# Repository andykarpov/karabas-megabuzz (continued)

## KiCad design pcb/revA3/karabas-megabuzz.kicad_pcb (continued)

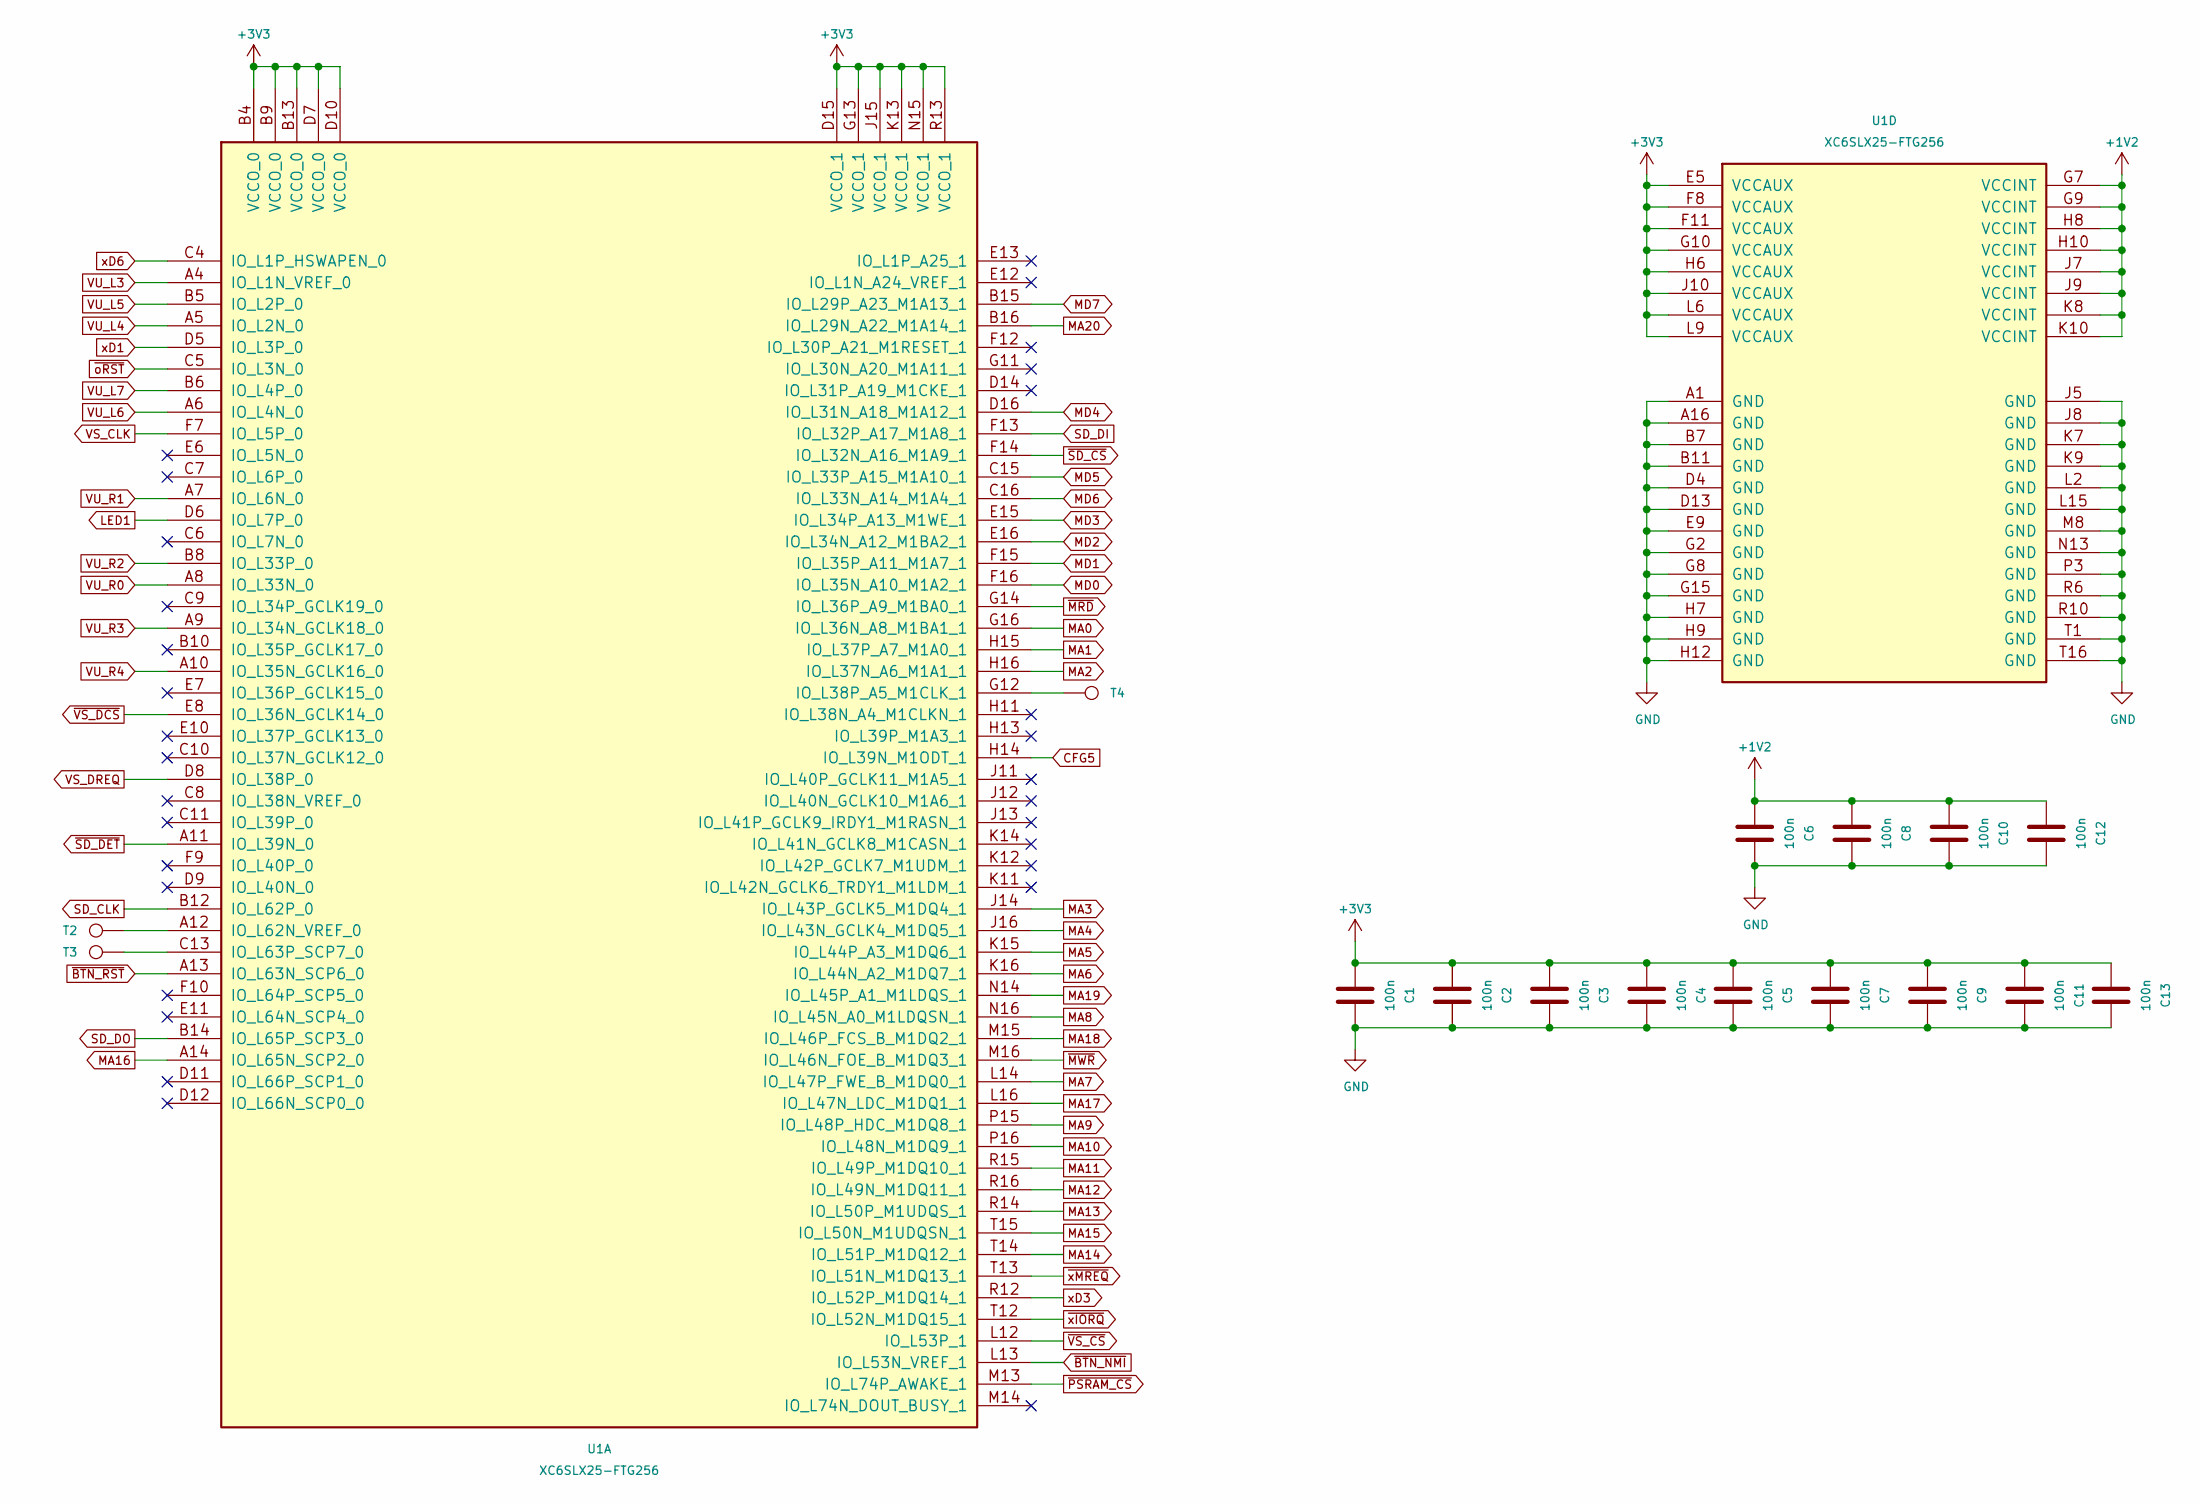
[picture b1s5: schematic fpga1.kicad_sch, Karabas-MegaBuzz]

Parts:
C1, C2, C3, C4, C5, C7, C9, C11, C13: 100n; C_0603_1608Metric_Pad1.08x0.95mm_HandSolder
C6, C8, C10, C12: 100n; C_0603_1608Metric
T2: TestPoint2; TestPoint_Pad_D1.5mm
T3, T4: TestPoint; TestPoint_Pad_D1.5mm
U1: XC6SLX25-FTG256; BGA-256_17.0x17.0mm_Layout16x16_P1.0mm_Ball0.5mm_Pad0.4mm_N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

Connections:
+1V2: C6.1, C8.1, C10.1, C12.1, U1.G7 (VCCINT), U1.G9 (VCCINT), U1.H8 (VCCINT), U1.H10 (VCCINT), U1.J7 (VCCINT), U1.J9 (VCCINT), U1.K8 (VCCINT), U1.K10 (VCCINT); also elsewhere on the board
+3V3: C1.1, C2.1, C3.1, C4.1, C5.1, C7.1, C9.1, C11.1, C13.1, U1.B4 (VCCO_0), U1.B9 (VCCO_0), U1.B13 (VCCO_0), U1.D7 (VCCO_0), U1.D10 (VCCO_0), U1.D15 (VCCO_1), U1.E5 (VCCAUX), U1.F8 (VCCAUX), U1.F11 (VCCAUX), U1.G10 (VCCAUX), U1.G13 (VCCO_1), U1.H6 (VCCAUX), U1.J10 (VCCAUX), U1.J15 (VCCO_1), U1.K13 (VCCO_1), U1.L6 (VCCAUX), U1.L9 (VCCAUX), U1.N15 (VCCO_1), U1.R13 (VCCO_1); also elsewhere on the board
CFG5: U1.H14 (IO_L39N_M1ODT_1); also elsewhere on the board
GND: C1.2, C2.2, C3.2, C4.2, C5.2, C6.2, C7.2, C8.2, C9.2, C10.2, C11.2, C12.2, C13.2, U1.A1 (GND), U1.A16 (GND), U1.B7 (GND), U1.B11 (GND), U1.D4 (GND), U1.D13 (GND), U1.E9 (GND), U1.G2 (GND), U1.G8 (GND), U1.G15 (GND), U1.H7 (GND), U1.H9 (GND), U1.H12 (GND), U1.J5 (GND), U1.J8 (GND), U1.K7 (GND), U1.K9 (GND), U1.L2 (GND), U1.L15 (GND), U1.M8 (GND), U1.N13 (GND), U1.P3 (GND), U1.R6 (GND), U1.R10 (GND), U1.T1 (GND), U1.T16 (GND); also elsewhere on the board
LED1: U1.D6 (IO_L7P_0); also elsewhere on the board
MA0: U1.G16 (IO_L36N_A8_M1BA1_1); also elsewhere on the board
MA1: U1.H15 (IO_L37P_A7_M1A0_1); also elsewhere on the board
MA2: U1.H16 (IO_L37N_A6_M1A1_1); also elsewhere on the board
MA3: U1.J14 (IO_L43P_GCLK5_M1DQ4_1); also elsewhere on the board
MA4: U1.J16 (IO_L43N_GCLK4_M1DQ5_1); also elsewhere on the board
MA5: U1.K15 (IO_L44P_A3_M1DQ6_1); also elsewhere on the board
MA6: U1.K16 (IO_L44N_A2_M1DQ7_1); also elsewhere on the board
MA7: U1.L14 (IO_L47P_FWE_B_M1DQ0_1); also elsewhere on the board
MA8: U1.N16 (IO_L45N_A0_M1LDQSN_1); also elsewhere on the board
MA9: U1.P15 (IO_L48P_HDC_M1DQ8_1); also elsewhere on the board
MA10: U1.P16 (IO_L48N_M1DQ9_1); also elsewhere on the board
MA11: U1.R15 (IO_L49P_M1DQ10_1); also elsewhere on the board
MA12: U1.R16 (IO_L49N_M1DQ11_1); also elsewhere on the board
MA13: U1.R14 (IO_L50P_M1UDQS_1); also elsewhere on the board
MA14: U1.T14 (IO_L51P_M1DQ12_1); also elsewhere on the board
MA15: U1.T15 (IO_L50N_M1UDQSN_1); also elsewhere on the board
MA16: U1.A14 (IO_L65N_SCP2_0); also elsewhere on the board
MA17: U1.L16 (IO_L47N_LDC_M1DQ1_1); also elsewhere on the board
MA18: U1.M15 (IO_L46P_FCS_B_M1DQ2_1); also elsewhere on the board
MA19: U1.N14 (IO_L45P_A1_M1LDQS_1); also elsewhere on the board
MA20: U1.B16 (IO_L29N_A22_M1A14_1); also elsewhere on the board
MD0: U1.F16 (IO_L35N_A10_M1A2_1); also elsewhere on the board
MD1: U1.F15 (IO_L35P_A11_M1A7_1); also elsewhere on the board
MD2: U1.E16 (IO_L34N_A12_M1BA2_1); also elsewhere on the board
MD3: U1.E15 (IO_L34P_A13_M1WE_1); also elsewhere on the board
MD4: U1.D16 (IO_L31N_A18_M1A12_1); also elsewhere on the board
MD5: U1.C15 (IO_L33P_A15_M1A10_1); also elsewhere on the board
MD6: U1.C16 (IO_L33N_A14_M1A4_1); also elsewhere on the board
MD7: U1.B15 (IO_L29P_A23_M1A13_1); also elsewhere on the board
unnamed: T4.1 (1_1), U1.G12 (IO_L38P_A5_M1CLK_1)
unnamed: T2.1 (1_1), U1.A12 (IO_L62N_VREF_0)
unnamed: T3.1 (1_1), U1.C13 (IO_L63P_SCP7_0)
SD_CLK: U1.B12 (IO_L62P_0); also elsewhere on the board
SD_DI: U1.F13 (IO_L32P_A17_M1A8_1); also elsewhere on the board
SD_DO: U1.B14 (IO_L65P_SCP3_0); also elsewhere on the board
VS_CLK: U1.F7 (IO_L5P_0); also elsewhere on the board
VS_DREQ: U1.D8 (IO_L38P_0); also elsewhere on the board
VU_L3: U1.A4 (IO_L1N_VREF_0); also elsewhere on the board
VU_L4: U1.A5 (IO_L2N_0); also elsewhere on the board
VU_L5: U1.B5 (IO_L2P_0); also elsewhere on the board
VU_L6: U1.A6 (IO_L4N_0); also elsewhere on the board
VU_L7: U1.B6 (IO_L4P_0); also elsewhere on the board
VU_R0: U1.A8 (IO_L33N_0); also elsewhere on the board
VU_R1: U1.A7 (IO_L6N_0); also elsewhere on the board
VU_R2: U1.B8 (IO_L33P_0); also elsewhere on the board
VU_R3: U1.A9 (IO_L34N_GCLK18_0); also elsewhere on the board
VU_R4: U1.A10 (IO_L35N_GCLK16_0); also elsewhere on the board
xD1: U1.D5 (IO_L3P_0); also elsewhere on the board
xD3: U1.R12 (IO_L52P_M1DQ14_1); also elsewhere on the board
xD6: U1.C4 (IO_L1P_HSWAPEN_0); also elsewhere on the board
~BTN_NMI: U1.L13 (IO_L53N_VREF_1); also elsewhere on the board
~BTN_RST: U1.A13 (IO_L63N_SCP6_0); also elsewhere on the board
~MRD: U1.G14 (IO_L36P_A9_M1BA0_1); also elsewhere on the board
~MWR: U1.M16 (IO_L46N_FOE_B_M1DQ3_1); also elsewhere on the board
~PSRAM_CS: U1.M13 (IO_L74P_AWAKE_1); also elsewhere on the board
~SD_CS: U1.F14 (IO_L32N_A16_M1A9_1); also elsewhere on the board
~SD_DET: U1.A11 (IO_L39N_0); also elsewhere on the board
~VS_CS: U1.L12 (IO_L53P_1); also elsewhere on the board
~VS_DCS: U1.E8 (IO_L36N_GCLK14_0); also elsewhere on the board
~oRST: U1.C5 (IO_L3N_0); also elsewhere on the board
~xIORQ: U1.T12 (IO_L52N_M1DQ15_1); also elsewhere on the board
~xMREQ: U1.T13 (IO_L51N_M1DQ13_1); also elsewhere on the board

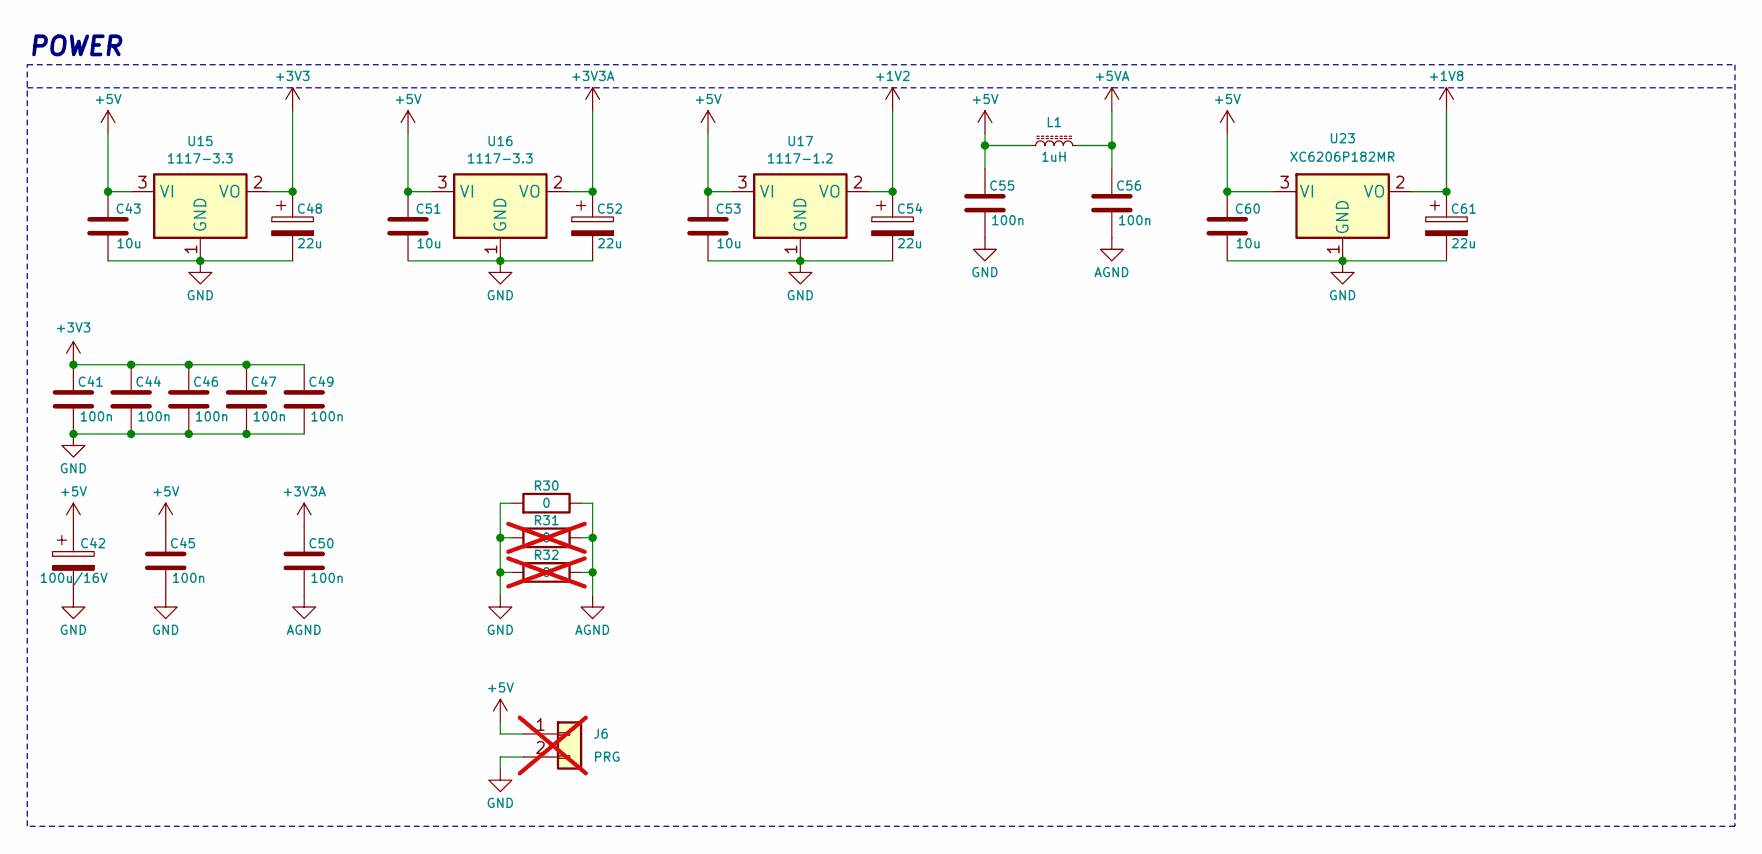
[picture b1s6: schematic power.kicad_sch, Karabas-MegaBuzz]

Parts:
C41, C44, C45, C46, C47, C49, C50, C55, C56: 100n; C_0603_1608Metric_Pad1.08x0.95mm_HandSolder
C42: 100u/16V; CP_EIA-6032-28_Kemet-C_HandSolder
C43, C51, C53, C60: 10u; C_0603_1608Metric_Pad1.08x0.95mm_HandSolder
C48, C52, C54, C61: 22u; CP_EIA-3216-18_Kemet-A_HandSolder
J6: PRG; PinHeader_1x02_P2.54mm_Vertical; not fitted
L1: 1uH; L_0603_1608Metric_Pad1.05x0.95mm_HandSolder
R30: 0; R_0603_1608Metric_Pad0.98x0.95mm_HandSolder
R31, R32: 0; R_0603_1608Metric_Pad0.98x0.95mm_HandSolder; not fitted
U15, U16: 1117-3.3; SOT-223-3_TabPin2
U17: 1117-1.2; SOT-223-3_TabPin2
U23: XC6206P182MR; SOT-23_Handsoldering

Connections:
+1V2: C54.1, U17.2 (VO); also elsewhere on the board
+1V8: C61.1, U23.2 (VO); also elsewhere on the board
+3V3: C41.1, C44.1, C46.1, C47.1, C48.1, C49.1, U15.2 (VO); also elsewhere on the board
+3V3A: C50.1, C52.1, U16.2 (VO); also elsewhere on the board
+5V: C42.1, C43.1, C45.2, C51.1, C53.1, C55.1, C60.1, J6.1, L1.1, U15.3 (VI), U16.3 (VI), U17.3 (VI), U23.3 (VI); also elsewhere on the board
+5VA: C56.1, L1.2; also elsewhere on the board
AGND: C50.2, C56.2, R30.1, R31.1, R32.1; also elsewhere on the board
GND: C41.2, C42.2, C43.2, C44.2, C45.1, C46.2, C47.2, C48.2, C49.2, C51.2, C52.2, C53.2, C54.2, C55.2, C60.2, C61.2, J6.2, R30.2, R31.2, R32.2, U15.1 (GND), U16.1 (GND), U17.1 (GND), U23.1 (GND); also elsewhere on the board

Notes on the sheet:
POWER

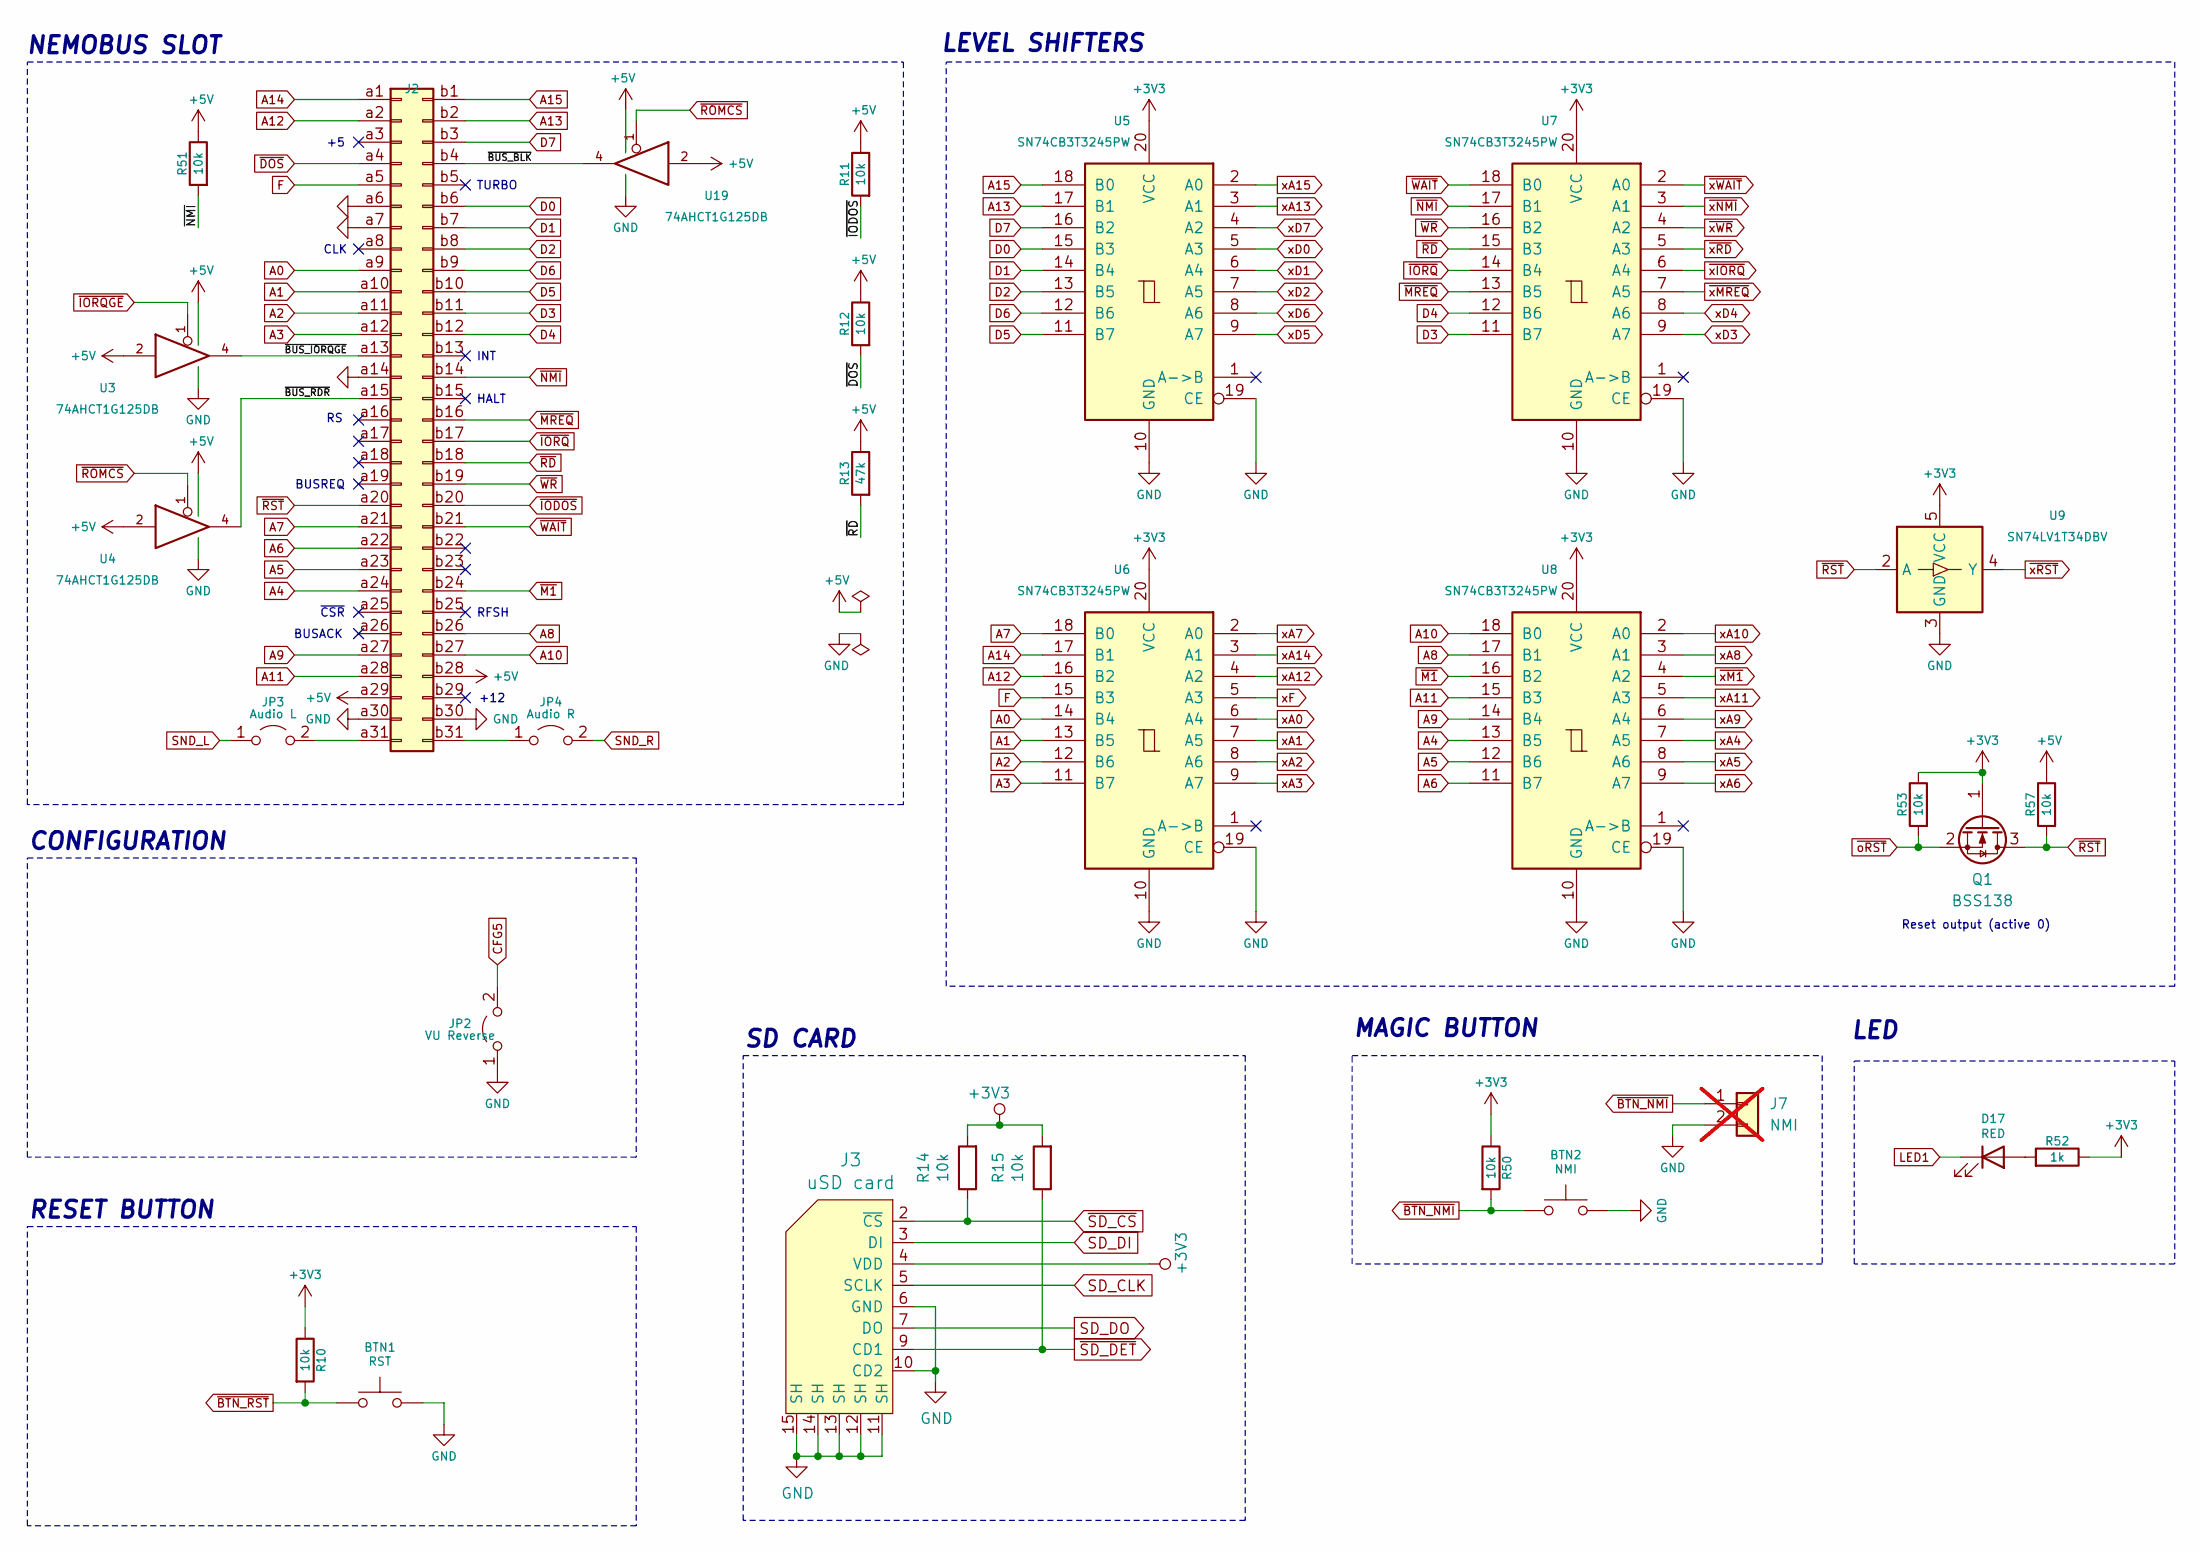
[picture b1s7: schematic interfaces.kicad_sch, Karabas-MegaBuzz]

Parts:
BTN1: RST; SW_SPST_PTS810_handsoldering
BTN2: NMI; SW_SPST_PTS810_handsoldering
D17: RED; LED_0603_1608Metric_Pad1.05x0.95mm_HandSolder
J2: Conn_02x31_Row_Letter_First; ZX_NEMO_62_EDGE
J3: uSD card; Conn_uSDcard
J7: NMI; PinHeader_1x02_P2.54mm_Vertical; not fitted
JP2: VU Reverse; SolderJumper-2_P1.3mm_Open_RoundedPad1.0x1.5mm
JP3: Audio L; SolderJumper-2_P1.3mm_Open_RoundedPad1.0x1.5mm
JP4: Audio R; SolderJumper-2_P1.3mm_Open_RoundedPad1.0x1.5mm
Q1: BSS138; SOT-23
R10, R11, R12, R14, R15, R50, R51, R53, R57: 10k; R_0603_1608Metric_Pad0.98x0.95mm_HandSolder
R13: 47k; R_0603_1608Metric_Pad0.98x0.95mm_HandSolder
R52: 1k; R_0603_1608Metric_Pad0.98x0.95mm_HandSolder
U3, U4, U19: 74AHCT1G125DB; SOT-23-5_HandSoldering
U5, U6, U7, U8: SN74CB3T3245PW; TSSOP-20_4.4x6.5mm_P0.65mm
U9: SN74LV1T34DBV; SOT-23-5_HandSoldering

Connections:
+3V3: J3.4 (VDD), Q1.1 (G), R10.1, R14.2, R15.2, R50.1, R52.1, R53.1, U5.20 (VCC), U6.20 (VCC), U7.20 (VCC), U8.20 (VCC), U9.5 (VCC); also elsewhere on the board
+5V: J2.a29, J2.b28, R11.1, R12.1, R13.1, R51.1, R57.1, U3.2, U3.5 (VCC), U4.2, U4.5 (VCC), U19.2, U19.5 (VCC); also elsewhere on the board
/Interfaces/~BUS_BLK: J2.b4, U19.4
/Interfaces/~BUS_IORQGE: J2.a13, U3.4
/Interfaces/~BUS_RDR: J2.a15, U4.4
A0: J2.a9, U6.14 (B4)
A1: J2.a10, U6.13 (B5)
A2: J2.a11, U6.12 (B6)
A3: J2.a12, U6.11 (B7)
A4: J2.a24, U8.13 (B5)
A5: J2.a23, U8.12 (B6)
A6: J2.a22, U8.11 (B7)
A7: J2.a21, U6.18 (B0)
A8: J2.b26, U8.17 (B1)
A9: J2.a27, U8.14 (B4)
A10: J2.b27, U8.18 (B0)
A11: J2.a28, U8.15 (B3)
A12: J2.a2, U6.16 (B2)
A13: J2.b2, U5.17 (B1)
A14: J2.a1, U6.17 (B1)
A15: J2.b1, U5.18 (B0)
CFG5: JP2.2 (B); also elsewhere on the board
D0: J2.b6, U5.15 (B3)
D1: J2.b7, U5.14 (B4)
D2: J2.b8, U5.13 (B5)
D3: J2.b11, U7.11 (B7)
D4: J2.b12, U7.12 (B6)
D5: J2.b10, U5.11 (B7)
D6: J2.b9, U5.12 (B6)
D7: J2.b3, U5.16 (B2)
F: J2.a5, U6.15 (B3)
GND: BTN1.2, BTN2.2, J2.a6, J2.a7, J2.a14, J2.a30, J2.b30, J3.6 (GND), J3.10 (CD2), J3.11 (SH), J3.12 (SH), J3.13 (SH), J3.14 (SH), J3.15 (SH), J7.2, JP2.1 (A), U3.3 (GND), U4.3 (GND), U5.10 (GND), U5.19 (CE), U6.10 (GND), U6.19 (CE), U7.10 (GND), U7.19 (CE), U8.10 (GND), U8.19 (CE), U9.3 (GND), U19.3 (GND); also elsewhere on the board
LED1: D17.1 (K); also elsewhere on the board
unnamed: D17.2 (A), R52.2
unnamed: J2.a31, JP3.2 (B)
unnamed: J2.b31, JP4.1 (A)
SD_CLK: J3.5 (SCLK); also elsewhere on the board
SD_DI: J3.3 (DI); also elsewhere on the board
SD_DO: J3.7 (DO); also elsewhere on the board
SND_L: JP3.1 (A); also elsewhere on the board
SND_R: JP4.2 (B); also elsewhere on the board
xA0: U6.6 (A4); also elsewhere on the board
xA1: U6.7 (A5); also elsewhere on the board
xA2: U6.8 (A6); also elsewhere on the board
xA3: U6.9 (A7); also elsewhere on the board
xA4: U8.7 (A5); also elsewhere on the board
xA5: U8.8 (A6); also elsewhere on the board
xA6: U8.9 (A7); also elsewhere on the board
xA7: U6.2 (A0); also elsewhere on the board
xA8: U8.3 (A1); also elsewhere on the board
xA9: U8.6 (A4); also elsewhere on the board
xA10: U8.2 (A0); also elsewhere on the board
xA11: U8.5 (A3); also elsewhere on the board
xA12: U6.4 (A2); also elsewhere on the board
xA13: U5.3 (A1); also elsewhere on the board
xA14: U6.3 (A1); also elsewhere on the board
xA15: U5.2 (A0); also elsewhere on the board
xD0: U5.5 (A3); also elsewhere on the board
xD1: U5.6 (A4); also elsewhere on the board
xD2: U5.7 (A5); also elsewhere on the board
xD3: U7.9 (A7); also elsewhere on the board
xD4: U7.8 (A6); also elsewhere on the board
xD5: U5.9 (A7); also elsewhere on the board
xD6: U5.8 (A6); also elsewhere on the board
xD7: U5.4 (A2); also elsewhere on the board
xF: U6.5 (A3); also elsewhere on the board
~BTN_NMI: BTN2.1, J7.1, R50.2; also elsewhere on the board
~BTN_RST: BTN1.1, R10.2; also elsewhere on the board
~DOS: J2.a4, R12.2
~IODOS: J2.b20, R11.2
~IORQGE: U3.1; also elsewhere on the board
~IORQ: J2.b17, U7.14 (B4)
~M1: J2.b24, U8.16 (B2)
~MREQ: J2.b16, U7.13 (B5)
~NMI: J2.b14, R51.2, U7.17 (B1)
~RD: J2.b18, R13.2, U7.15 (B3)
~ROMCS: U4.1, U19.1; also elsewhere on the board
~RST: J2.a20, Q1.3 (D), R57.2, U9.2 (A)
~SD_CS: J3.2 (~CS), R14.1; also elsewhere on the board
~SD_DET: J3.9 (CD1), R15.1; also elsewhere on the board
~WAIT: J2.b21, U7.18 (B0)
~WR: J2.b19, U7.16 (B2)
~oRST: Q1.2 (S), R53.2; also elsewhere on the board
~xIORQ: U7.6 (A4); also elsewhere on the board
~xM1: U8.4 (A2); also elsewhere on the board
~xMREQ: U7.7 (A5); also elsewhere on the board
~xNMI: U7.3 (A1); also elsewhere on the board
~xRD: U7.5 (A3); also elsewhere on the board
~xRST: U9.4 (Y); also elsewhere on the board
~xWAIT: U7.2 (A0); also elsewhere on the board
~xWR: U7.4 (A2); also elsewhere on the board

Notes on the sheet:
BUSREQ
SD CARD
CLK
CONFIGURATION
RFSH
Reset output (active 0)
+12
HALT
LEVEL SHIFTERS
TURBO
LED
~{CSR}
NEMOBUS SLOT
RESET BUTTON
BUSACK
MAGIC BUTTON
INT

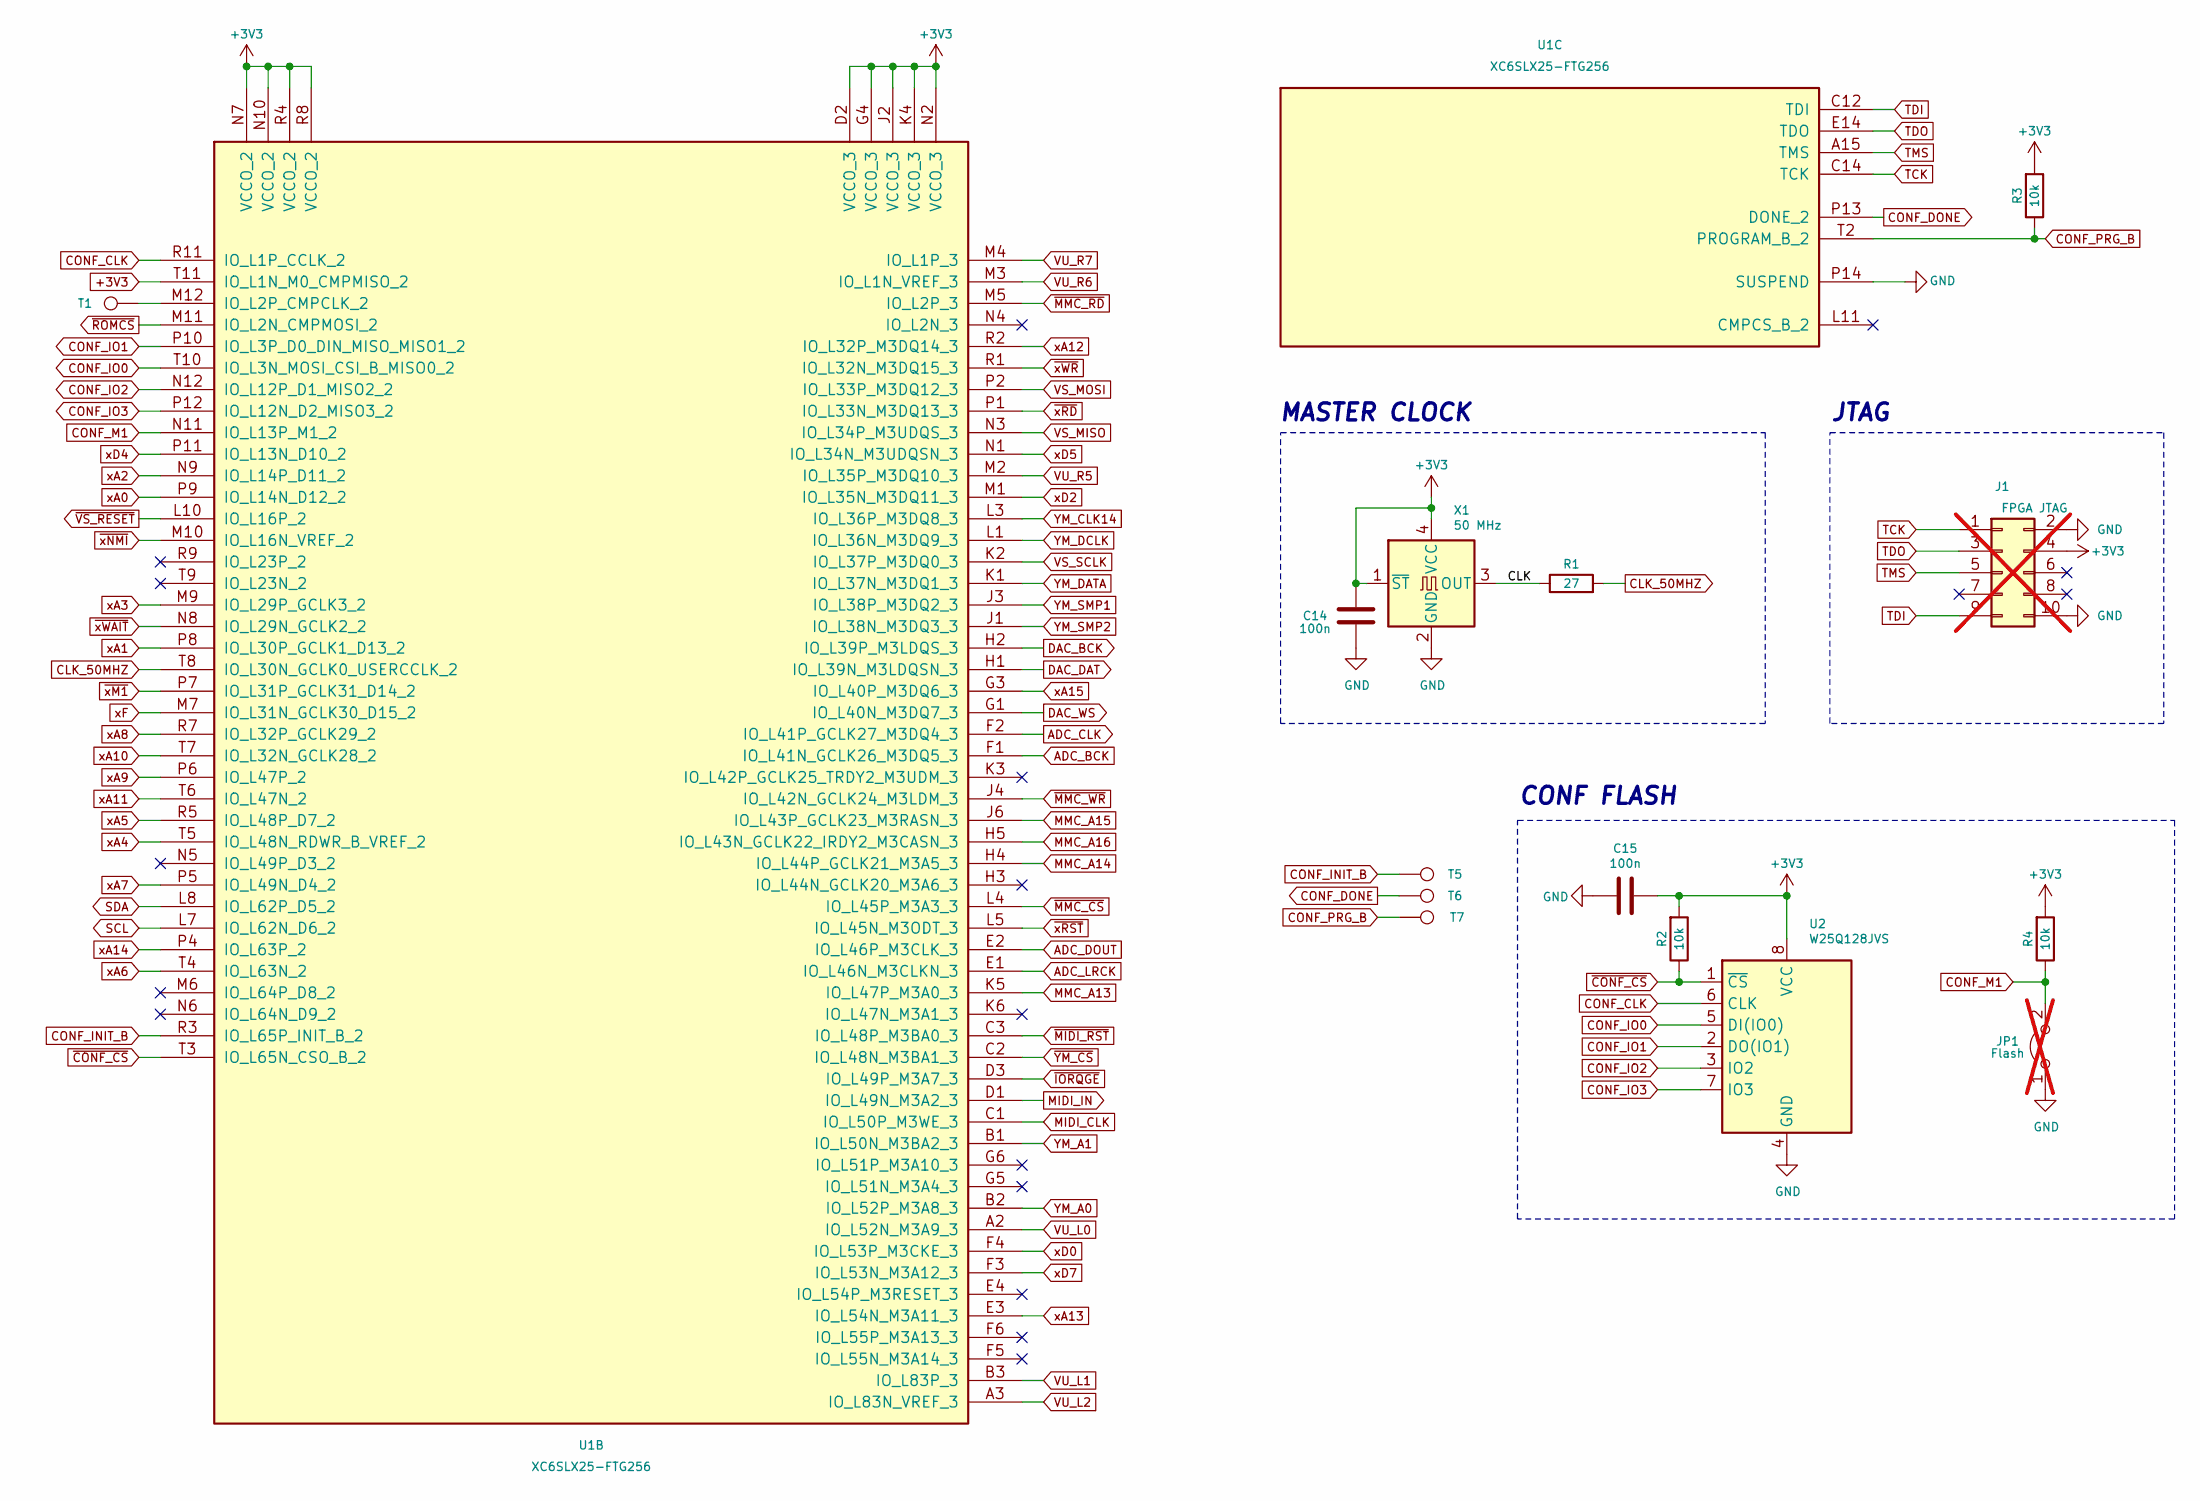
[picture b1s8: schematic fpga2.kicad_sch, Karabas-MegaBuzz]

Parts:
C14, C15: 100n; C_0603_1608Metric_Pad1.08x0.95mm_HandSolder
J1: FPGA JTAG; PinHeader_2x05_P2.54mm_Vertical; not fitted
JP1: Flash; SolderJumper-2_P1.3mm_Bridged_RoundedPad1.0x1.5mm; not fitted
R1: 27; R_0603_1608Metric_Pad0.98x0.95mm_HandSolder
R2, R3, R4: 10k; R_0603_1608Metric_Pad0.98x0.95mm_HandSolder
T1: TestPoint1; TestPoint_Pad_D1.5mm
T5, T6, T7: TestPoint; TestPoint_Pad_D1.5mm
U1: XC6SLX25-FTG256; BGA-256_17.0x17.0mm_Layout16x16_P1.0mm_Ball0.5mm_Pad0.4mm_N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
U2: W25Q128JVS; SOIC-8_5.3x5.3mm_P1.27mm
X1: 50 MHz; Oscillator_SMD_SeikoEpson_SG8002CA-4Pin_7.0x5.0mm

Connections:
+3V3: C14.1, C15.1, J1.4, R2.2, R3.2, R4.2, U1.D2 (VCCO_3), U1.G4 (VCCO_3), U1.J2 (VCCO_3), U1.K4 (VCCO_3), U1.N2 (VCCO_3), U1.N7 (VCCO_2), U1.N10 (VCCO_2), U1.R4 (VCCO_2), U1.R8 (VCCO_2), U1.T11 (IO_L1N_M0_CMPMISO_2), U2.8 (VCC), X1.1 (~ST), X1.4 (VCC); also elsewhere on the board
/FPGA2/CLK: R1.1, X1.3 (OUT)
ADC_BCK: U1.F1 (IO_L41N_GCLK26_M3DQ5_3); also elsewhere on the board
ADC_CLK: U1.F2 (IO_L41P_GCLK27_M3DQ4_3); also elsewhere on the board
ADC_DOUT: U1.E2 (IO_L46P_M3CLK_3); also elsewhere on the board
ADC_LRCK: U1.E1 (IO_L46N_M3CLKN_3); also elsewhere on the board
CLK_50MHZ: R1.2, U1.T8 (IO_L30N_GCLK0_USERCCLK_2)
CONF_CLK: U1.R11 (IO_L1P_CCLK_2), U2.6 (CLK); also elsewhere on the board
CONF_DONE: T6.1 (1_1), U1.P13 (DONE_2)
CONF_INIT_B: T5.1 (1_1), U1.R3 (IO_L65P_INIT_B_2)
CONF_IO0: U1.T10 (IO_L3N_MOSI_CSI_B_MISO0_2), U2.5 (DI(IO0)); also elsewhere on the board
CONF_IO1: U1.P10 (IO_L3P_D0_DIN_MISO_MISO1_2), U2.2 (DO(IO1)); also elsewhere on the board
CONF_IO2: U1.N12 (IO_L12P_D1_MISO2_2), U2.3 (IO2); also elsewhere on the board
CONF_IO3: U1.P12 (IO_L12N_D2_MISO3_2), U2.7 (IO3); also elsewhere on the board
CONF_M1: JP1.2 (B), R4.1, U1.N11 (IO_L13P_M1_2)
CONF_PRG_B: R3.1, T7.1 (1_1), U1.T2 (PROGRAM_B_2)
DAC_BCK: U1.H2 (IO_L39P_M3LDQS_3); also elsewhere on the board
DAC_DAT: U1.H1 (IO_L39N_M3LDQSN_3); also elsewhere on the board
DAC_WS: U1.G1 (IO_L40N_M3DQ7_3); also elsewhere on the board
GND: C14.2, C15.2, J1.2, J1.10, JP1.1 (A), U1.P14 (SUSPEND), U2.4 (GND), X1.2 (GND); also elsewhere on the board
MIDI_CLK: U1.C1 (IO_L50P_M3WE_3); also elsewhere on the board
MIDI_IN: U1.D1 (IO_L49N_M3A2_3); also elsewhere on the board
MMC_A13: U1.K5 (IO_L47P_M3A0_3); also elsewhere on the board
MMC_A14: U1.H4 (IO_L44P_GCLK21_M3A5_3); also elsewhere on the board
MMC_A15: U1.J6 (IO_L43P_GCLK23_M3RASN_3); also elsewhere on the board
MMC_A16: U1.H5 (IO_L43N_GCLK22_IRDY2_M3CASN_3); also elsewhere on the board
unnamed: T1.1 (1_1), U1.M12 (IO_L2P_CMPCLK_2)
SCL: U1.L7 (IO_L62N_D6_2); also elsewhere on the board
SDA: U1.L8 (IO_L62P_D5_2); also elsewhere on the board
TCK: J1.1, U1.C14 (TCK)
TDI: J1.9, U1.C12 (TDI)
TDO: J1.3, U1.E14 (TDO)
TMS: J1.5, U1.A15 (TMS)
VS_MISO: U1.N3 (IO_L34P_M3UDQS_3); also elsewhere on the board
VS_MOSI: U1.P2 (IO_L33P_M3DQ12_3); also elsewhere on the board
VS_SCLK: U1.K2 (IO_L37P_M3DQ0_3); also elsewhere on the board
VU_L0: U1.A2 (IO_L52N_M3A9_3); also elsewhere on the board
VU_L1: U1.B3 (IO_L83P_3); also elsewhere on the board
VU_L2: U1.A3 (IO_L83N_VREF_3); also elsewhere on the board
VU_R5: U1.M2 (IO_L35P_M3DQ10_3); also elsewhere on the board
VU_R6: U1.M3 (IO_L1N_VREF_3); also elsewhere on the board
VU_R7: U1.M4 (IO_L1P_3); also elsewhere on the board
YM_A0: U1.B2 (IO_L52P_M3A8_3); also elsewhere on the board
YM_A1: U1.B1 (IO_L50N_M3BA2_3); also elsewhere on the board
YM_CLK14: U1.L3 (IO_L36P_M3DQ8_3); also elsewhere on the board
YM_DATA: U1.K1 (IO_L37N_M3DQ1_3); also elsewhere on the board
YM_DCLK: U1.L1 (IO_L36N_M3DQ9_3); also elsewhere on the board
YM_SMP1: U1.J3 (IO_L38P_M3DQ2_3); also elsewhere on the board
YM_SMP2: U1.J1 (IO_L38N_M3DQ3_3); also elsewhere on the board
xA0: U1.P9 (IO_L14N_D12_2); also elsewhere on the board
xA1: U1.P8 (IO_L30P_GCLK1_D13_2); also elsewhere on the board
xA2: U1.N9 (IO_L14P_D11_2); also elsewhere on the board
xA3: U1.M9 (IO_L29P_GCLK3_2); also elsewhere on the board
xA4: U1.T5 (IO_L48N_RDWR_B_VREF_2); also elsewhere on the board
xA5: U1.R5 (IO_L48P_D7_2); also elsewhere on the board
xA6: U1.T4 (IO_L63N_2); also elsewhere on the board
xA7: U1.P5 (IO_L49N_D4_2); also elsewhere on the board
xA8: U1.R7 (IO_L32P_GCLK29_2); also elsewhere on the board
xA9: U1.P6 (IO_L47P_2); also elsewhere on the board
xA10: U1.T7 (IO_L32N_GCLK28_2); also elsewhere on the board
xA11: U1.T6 (IO_L47N_2); also elsewhere on the board
xA12: U1.R2 (IO_L32P_M3DQ14_3); also elsewhere on the board
xA13: U1.E3 (IO_L54N_M3A11_3); also elsewhere on the board
xA14: U1.P4 (IO_L63P_2); also elsewhere on the board
xA15: U1.G3 (IO_L40P_M3DQ6_3); also elsewhere on the board
xD0: U1.F4 (IO_L53P_M3CKE_3); also elsewhere on the board
xD2: U1.M1 (IO_L35N_M3DQ11_3); also elsewhere on the board
xD4: U1.P11 (IO_L13N_D10_2); also elsewhere on the board
xD5: U1.N1 (IO_L34N_M3UDQSN_3); also elsewhere on the board
xD7: U1.F3 (IO_L53N_M3A12_3); also elsewhere on the board
xF: U1.M7 (IO_L31N_GCLK30_D15_2); also elsewhere on the board
~CONF_CS: R2.1, U1.T3 (IO_L65N_CSO_B_2), U2.1 (~CS)
~IORQGE: U1.D3 (IO_L49P_M3A7_3); also elsewhere on the board
~MIDI_RST: U1.C3 (IO_L48P_M3BA0_3); also elsewhere on the board
~MMC_CS: U1.L4 (IO_L45P_M3A3_3); also elsewhere on the board
~MMC_RD: U1.M5 (IO_L2P_3); also elsewhere on the board
~MMC_WR: U1.J4 (IO_L42N_GCLK24_M3LDM_3); also elsewhere on the board
~ROMCS: U1.M11 (IO_L2N_CMPMOSI_2); also elsewhere on the board
~VS_RESET: U1.L10 (IO_L16P_2); also elsewhere on the board
~YM_CS: U1.C2 (IO_L48N_M3BA1_3); also elsewhere on the board
~xM1: U1.P7 (IO_L31P_GCLK31_D14_2); also elsewhere on the board
~xNMI: U1.M10 (IO_L16N_VREF_2); also elsewhere on the board
~xRD: U1.P1 (IO_L33N_M3DQ13_3); also elsewhere on the board
~xRST: U1.L5 (IO_L45N_M3ODT_3); also elsewhere on the board
~xWAIT: U1.N8 (IO_L29N_GCLK2_2); also elsewhere on the board
~xWR: U1.R1 (IO_L32N_M3DQ15_3); also elsewhere on the board

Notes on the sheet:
CONF FLASH
JTAG
MASTER CLOCK
